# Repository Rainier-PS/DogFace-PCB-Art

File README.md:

# DogFace PCB Art Keychain

DogFace is a custom dog-shaped PCB art keychain that lights up, vibrates, and reacts to button presses. This project is built around fun, interactivity, and portability — all packed into a single board you can hang on your bag, keys, or lanyard.

---

## Features

- 2 LEDs as glowing eyes
- 3 buttons:
  - Left eye control
  - Right eye control
  - Mouth "bark" via vibration motor
- 1 potentiometer to control LED brightness
- 1 capacitor to protect the motor circuit
- 5.3 mm keychain hole for easy attachment

---

## Bill of Materials (BoM)

| Component                      | Quantity         | Notes                                       |
|-------------------------------|------------------|---------------------------------------------|
| 5mm LED                       | 2                | Eyes                                        |
| Tactile Pushbutton (THT)      | 3                | Left eye, right eye, motor trigger          |
| Vibration Motor               | 1                | Tongue effect / "bark" vibration            |
| Potentiometer                 | 1                | LED brightness control                      |
| Capacitor                     | 1                | Motor protection (flyback damping)          |
| Resistors                     | 2                | Current limiting                            |
| Custom-shaped PCB             | 1                | Fabricated from this repo’s Gerber files    |
| Breadboard (for testing)      | 1                | For final circuit checks before soldering   |
| Jumper wires (male–male)      | 10               | For temporary connections on breadboard     |

---

## Note on Breadboard and Jumper Wires

Although this is a custom PCB project, I would like to include 1 breadboard and 10 male-to-male jumper wires in the kit to:

- Validate the full circuit functionality before soldering
- Test component behavior such as the motor, potentiometer, and transistor
- Ensure everything works as expected before committing to assembly

This is especially helpful since this is my first PCB project using KiCad.

---

## Screenshots

### Schematic  

### PCB Layout  

### 3D View  

---

## Files Included

- `/images/`: Schematic, layout, and 3D preview images
- `/production/`: Gerber and drill files ready for manufacturing
- `/PCB/`: KiCad Schematics and PCB Design
- This `README.md`

---

## Slack Username

`@Rainier P.S.`

---

## Reflections

This is my first-ever PCB project, and I built it completely in KiCad. I challenged myself to combine functionality with personality by making a usable and fun keychain circuit.

### What I Learned

- Creating expressive PCB art using DXF outlines
- Designing within tight space constraints

### Challenges

- Fitting all components onto the face without breaking the aesthetic
- Creating custom PCB designs using DXF outlines

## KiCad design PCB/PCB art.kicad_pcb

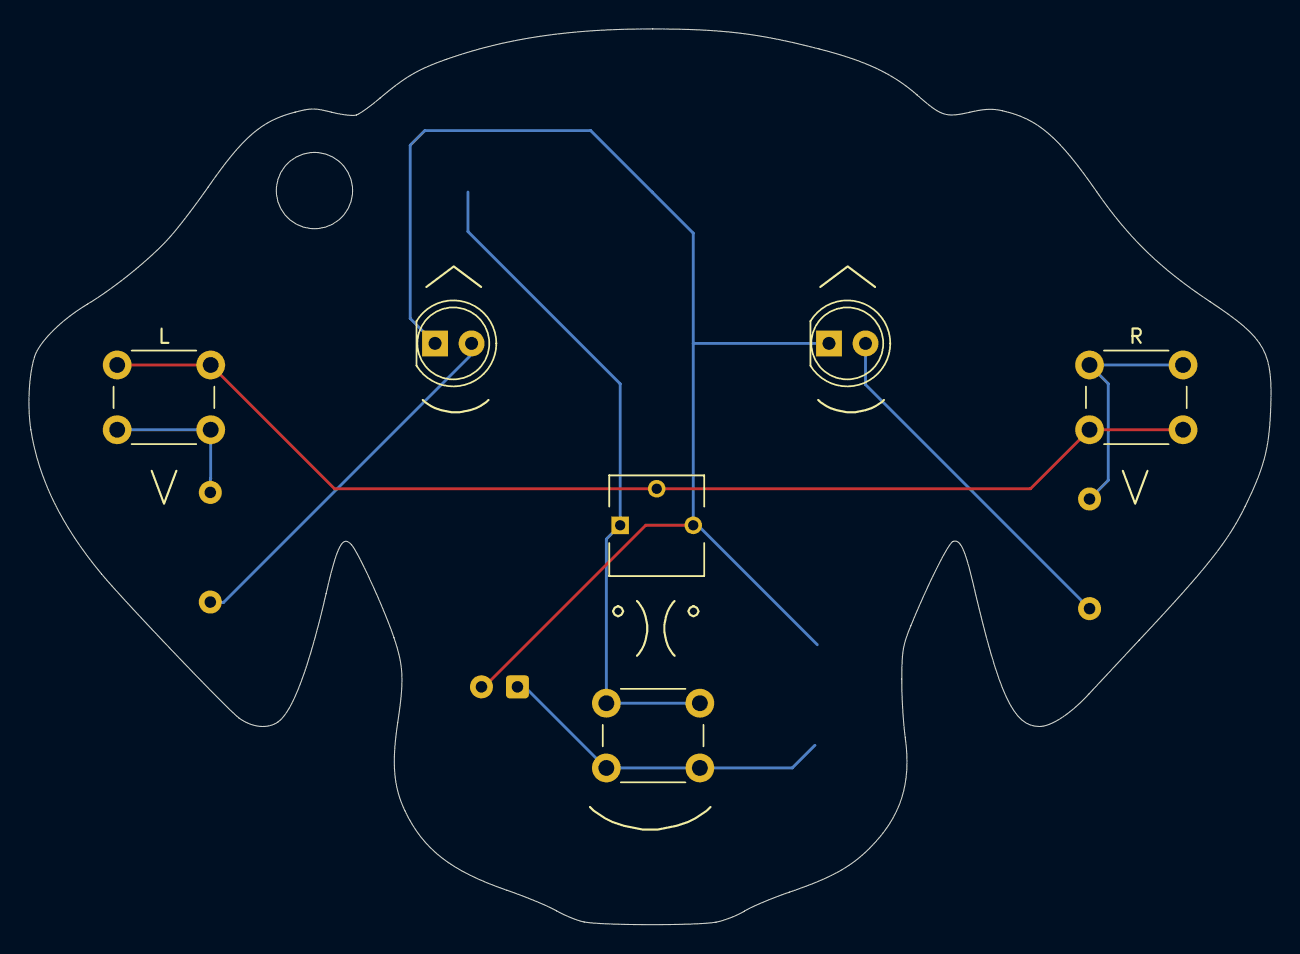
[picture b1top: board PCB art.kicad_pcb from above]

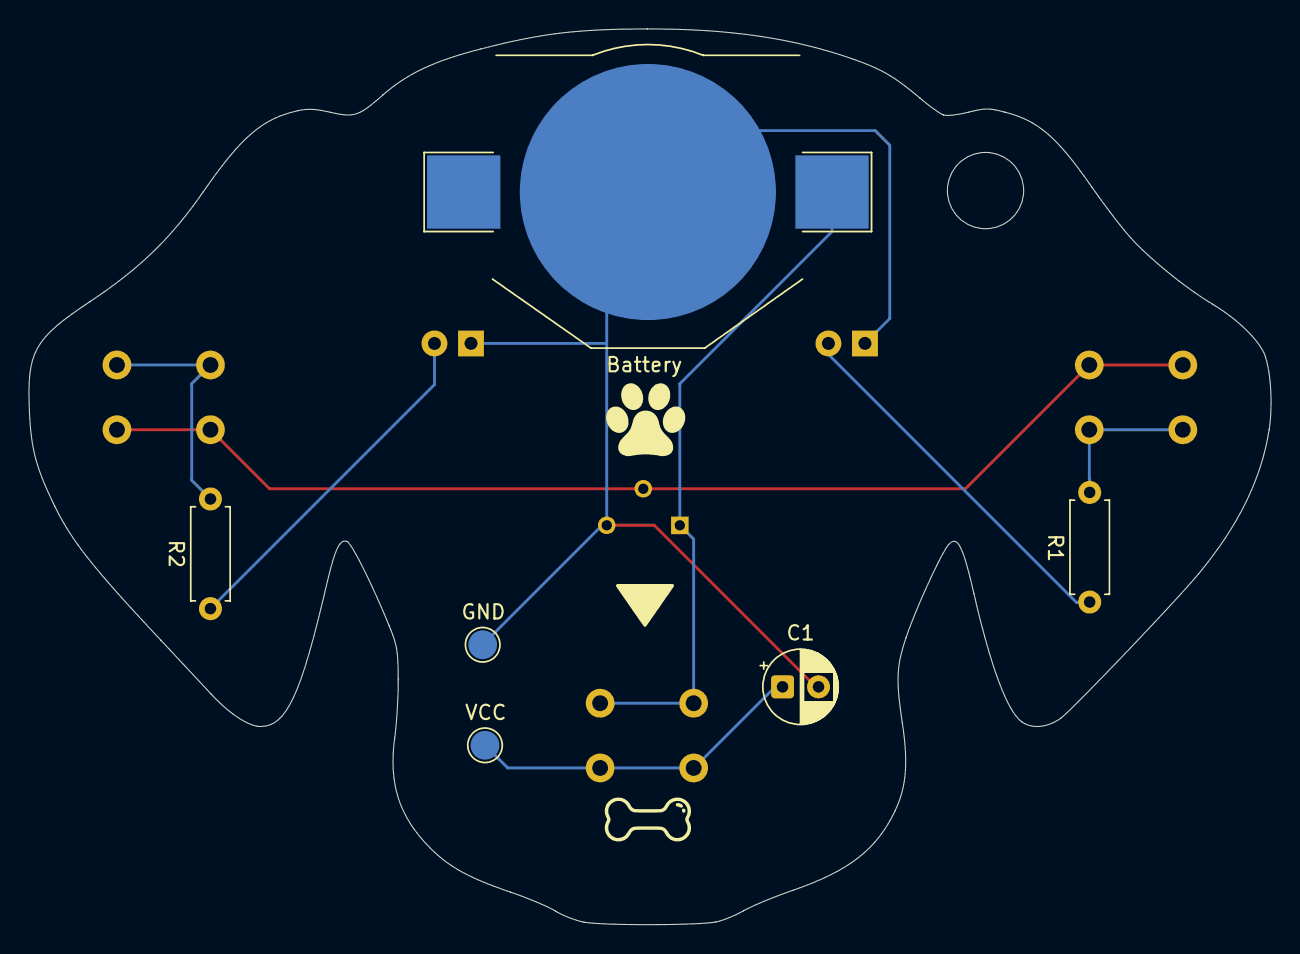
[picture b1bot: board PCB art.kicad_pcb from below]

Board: 2 copper layers, 86.3 x 62.3 mm, 12 parts (6 on the bottom side), 7 nets.

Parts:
<>: 3362P-1-103; TRIM_3362P-1-103
Battery: Battery_Cell; BatteryHolder_Keystone_3002_1x2032
C1: C; CP_Radial_D5.0mm_P2.50mm
GND: Motor_DC; TestPoint_Pad_D2.0mm
L: SW_Push; SW_PUSH_6mm_H9.5mm
R: SW_Push; SW_PUSH_6mm_H9.5mm
R1, R2: R; R_Axial_DIN0207_L6.3mm_D2.5mm_P7.62mm_Horizontal
VCC: Motor_DC; TestPoint_Pad_D2.0mm
^: LED; LED_D5.0mm
^#2: LED; LED_D5.0mm
|

: SW_Push; SW_PUSH_6mm_H9.5mm

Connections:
unnamed: <>.1, <>.2, Battery.1 (+), L.1, R.2, |.1
unnamed: <>.3, Battery.2 (-), C1.2, GND.1 (+), ^.1 (K), ^#2.1 (K)
unnamed: R1.1, ^#2.2 (A)
unnamed: R2.2, ^.2 (A)
unnamed: C1.1, VCC.1 (+), |.2
unnamed: L.2, R1.2
unnamed: R.1, R2.1

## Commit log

2025-06-28 Create Temp
